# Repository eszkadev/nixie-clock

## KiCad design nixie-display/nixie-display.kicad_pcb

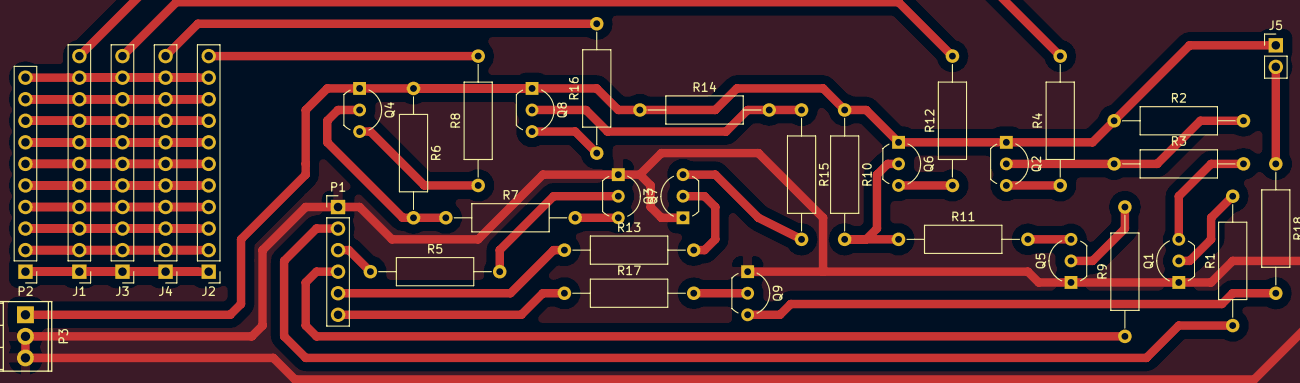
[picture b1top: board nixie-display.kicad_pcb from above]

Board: 2 copper layers, 35 parts (0 on the bottom side), 40 nets.

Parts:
J1, J2, J3, J4: Conn_01x11; Socket_Strip_Straight_1x11_Pitch2.54mm
J5: Conn_01x02; Socket_Strip_Straight_1x02_Pitch2.54mm
P1: CONN_01X06; Socket_Strip_Straight_1x06_Pitch2.54mm
P2: CONN_01X10; Socket_Strip_Straight_1x10_Pitch2.54mm
P3: CONN_01X03; TerminalBlock_Pheonix_MPT-2.54mm_3pol
Q1, Q3, Q5, Q7, Q9: MPSA42; TO-92_Inline_Wide
Q2, Q4, Q6, Q8: MPSA92; TO-92_Inline_Wide
R1, R5, R9, R13, R17: 33K; R_Axial_DIN0309_L9.0mm_D3.2mm_P15.24mm_Horizontal
R2, R6, R10, R14: 100K; R_Axial_DIN0309_L9.0mm_D3.2mm_P15.24mm_Horizontal
R3, R7, R11, R15: 470K; R_Axial_DIN0309_L9.0mm_D3.2mm_P15.24mm_Horizontal
R4, R8, R12, R16: 47K; R_Axial_DIN0309_L9.0mm_D3.2mm_P15.24mm_Horizontal
R18: 220K; R_Axial_DIN0309_L9.0mm_D3.2mm_P15.24mm_Horizontal

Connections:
GND: P1.1, P3.2, P3.3, Q1.1, Q3.1, Q5.1, Q7.1, Q9.1
unnamed: J1.1, J2.1, J3.1, J4.1, P2.1
unnamed: J1.2, J2.2, J3.2, J4.2, P2.2
unnamed: J1.3, J2.3, J3.3, J4.3, P2.3
unnamed: J1.4, J2.4, J3.4, J4.4, P2.4
unnamed: J1.5, J2.5, J3.5, J4.5, P2.5
unnamed: J1.6, J2.6, J3.6, J4.6, P2.6
unnamed: J1.7, J2.7, J3.7, J4.7, P2.7
unnamed: J1.8, J2.8, J3.8, J4.8, P2.8
unnamed: J1.9, J2.9, J3.9, J4.9, P2.9
unnamed: J1.10, J2.10, J3.10, J4.10, P2.10
unnamed: J1.11, R4.2
unnamed: J2.11, R8.2
unnamed: J3.11, R12.2
unnamed: J4.11, R16.2
unnamed: J5.2, R18.1
unnamed: P1.2, R1.1
unnamed: P1.3, R5.1
unnamed: P1.4, R9.1
unnamed: P1.5, R13.1
unnamed: P1.6, R17.1
unnamed: Q1.2, R1.2
unnamed: Q1.3, R3.2
unnamed: Q2.2, R2.2, R3.1
unnamed: Q2.3, R4.1
unnamed: Q3.2, R5.2
unnamed: Q3.3, R7.2
unnamed: Q4.2, R6.2, R7.1
unnamed: Q4.3, R8.1
unnamed: Q5.2, R9.2
unnamed: Q5.3, R11.2
unnamed: Q6.2, R10.2, R11.1
unnamed: Q6.3, R12.1
unnamed: Q7.2, R13.2
unnamed: Q7.3, R15.2
unnamed: Q8.2, R14.2, R15.1
unnamed: Q8.3, R16.1
unnamed: Q9.2, R17.2
unnamed: Q9.3, R18.2
VCC: J5.1, P3.1, Q2.1, Q4.1, Q6.1, Q8.1, R2.1, R6.1, R10.1, R14.1

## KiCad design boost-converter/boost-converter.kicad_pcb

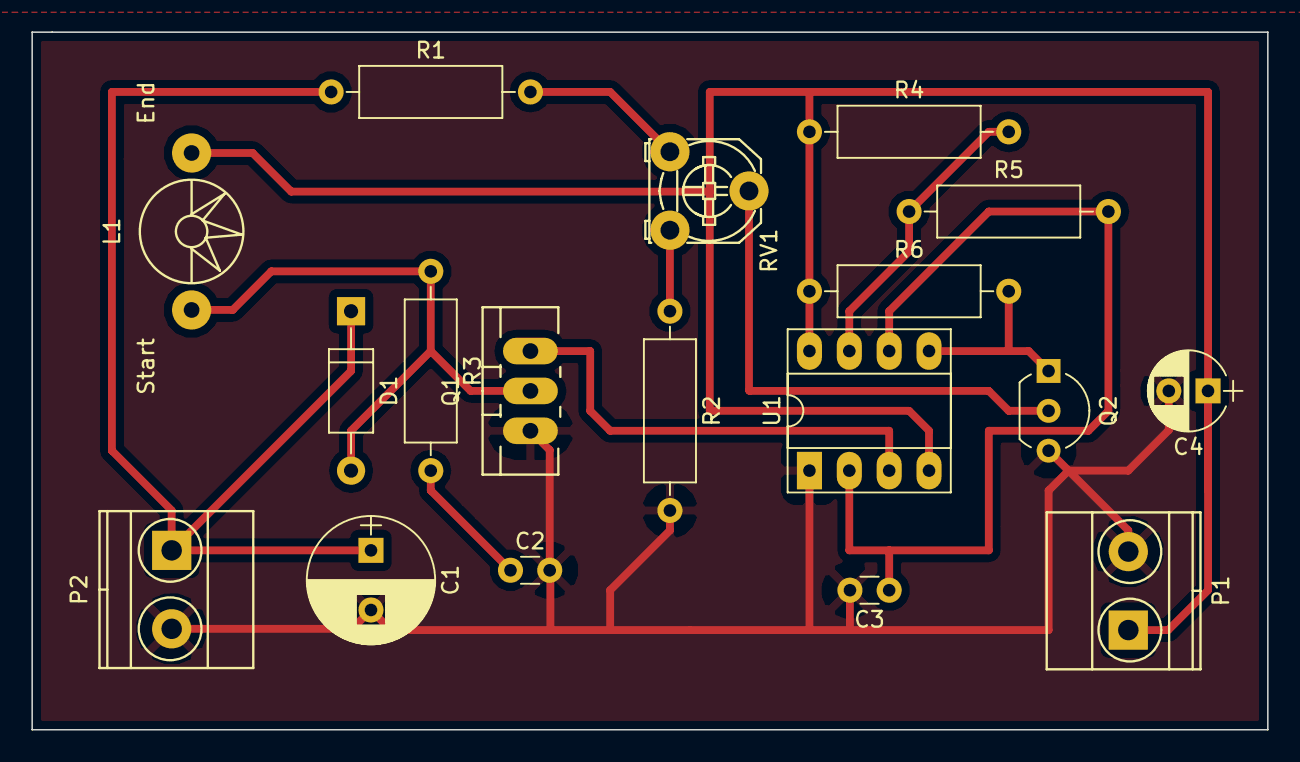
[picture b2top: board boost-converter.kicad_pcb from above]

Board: 2 copper layers, 78.7 x 44.4 mm, 18 parts (0 on the bottom side), 12 nets.

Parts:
C1: 2.2uF; CP_Radial_D8.0mm_P3.80mm
C2: 100pF; C_Disc_D3.0mm_W1.6mm_P2.50mm
C3: 2n2; C_Disc_D3.0mm_W1.6mm_P2.50mm
C4: 330uF; CP_Radial_D5.0mm_P2.50mm
D1: UF4004; D_A-405_P10.16mm_Horizontal
L1: 100uH; Choke_Toroid_horizontal_Diameter7-5mm_Amidon-T25
P1, P2: CONN_02X01; TerminalBlock_Pheonix_MKDS1.5-2pol
Q1: IRF730; TO-220_Neutral123_Vertical_LargePads
Q2: BC547; TO-92_Inline_Wide
R1: 220k; R_Axial_DIN0309_L9.0mm_D3.2mm_P12.70mm_Horizontal
R2: 470R; R_Axial_DIN0309_L9.0mm_D3.2mm_P12.70mm_Horizontal
R3: 2k2; R_Axial_DIN0309_L9.0mm_D3.2mm_P12.70mm_Horizontal
R4: 1k; R_Axial_DIN0309_L9.0mm_D3.2mm_P12.70mm_Horizontal
R5: 10k; R_Axial_DIN0309_L9.0mm_D3.2mm_P12.70mm_Horizontal
R6: 56k; R_Axial_DIN0309_L9.0mm_D3.2mm_P12.70mm_Horizontal
RV1: 1k; Potentiometer_Triwood_RM-065
U1: NE555; DIP-8_W7.62mm_Socket_LongPads

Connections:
+9V: C4.1, L1.2, P1.1, R4.1, R6.1, U1.4, U1.8
Earth: C1.2, C2.2, C3.2, C4.2, P1.2, P2.2, Q1.1, Q2.3, R2.2, U1.1
unnamed: C2.1, R3.2
unnamed: C3.1, R5.2, U1.2, U1.6
unnamed: D1.2, L1.1, Q1.2, R3.1
unnamed: Q1.3, U1.3
unnamed: Q2.1, R6.2, U1.5
unnamed: Q2.2, RV1.2
unnamed: R1.2, RV1.1
unnamed: R2.1, RV1.3
unnamed: R4.2, R5.1, U1.7
VSSA: C1.1, D1.1, P2.1, R1.1

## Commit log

2017-02-01 Boost converter schematic
2017-02-01 Zmiana footprintu potencjometru
2017-02-04 Dokończone pcb + pdf
2017-02-16 Atmega code
2017-02-17 Test RTC: read seconds
2017-02-17 Reading all data from RTC
2017-02-17 Set current time
2017-02-17 Added timer interrupt
2017-02-17 Added time setup over uart
2017-02-17 Better string formatting
2017-02-17 Added buzzer support
2017-03-04 Added nixie KiCad library with IN-12B symbol
2017-03-04 Added KiCad footprint for IN-12B tube
2017-03-04 Added tubes to the schematic and footprint library path
2017-03-04 Added neon tube lamp to the nixie library
2017-03-04 Nixie display schematic
2017-03-04 Added PWR_FLAG
2017-03-04 Assigned footprints
2017-12-05 Finished nixie-display pcb
2017-12-21 Second pcb version with different size
2017-12-23 Atmega328, multiplexing
2017-12-24 Always show number
2017-12-29 First test
2017-12-30 Add switch for RTC
2018-01-08 Arduino sketch for NodeMCU
2018-01-08 Enabled RTC
2018-01-08 Correct digits to my wiring
2018-01-08 Working second timer for at16
2018-01-08 Working time displaying
2018-01-15 tab -> space
2018-01-15 Added labels to scheme
2018-01-15 Correct dir for arduiono sketch
2018-01-15 Remove unused code
2018-03-03 Added photo
